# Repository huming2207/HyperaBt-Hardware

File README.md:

# HyperaBt-Hardware

Converting USB Keyboard to Bluetooth, for PC, smart phones and tablets!

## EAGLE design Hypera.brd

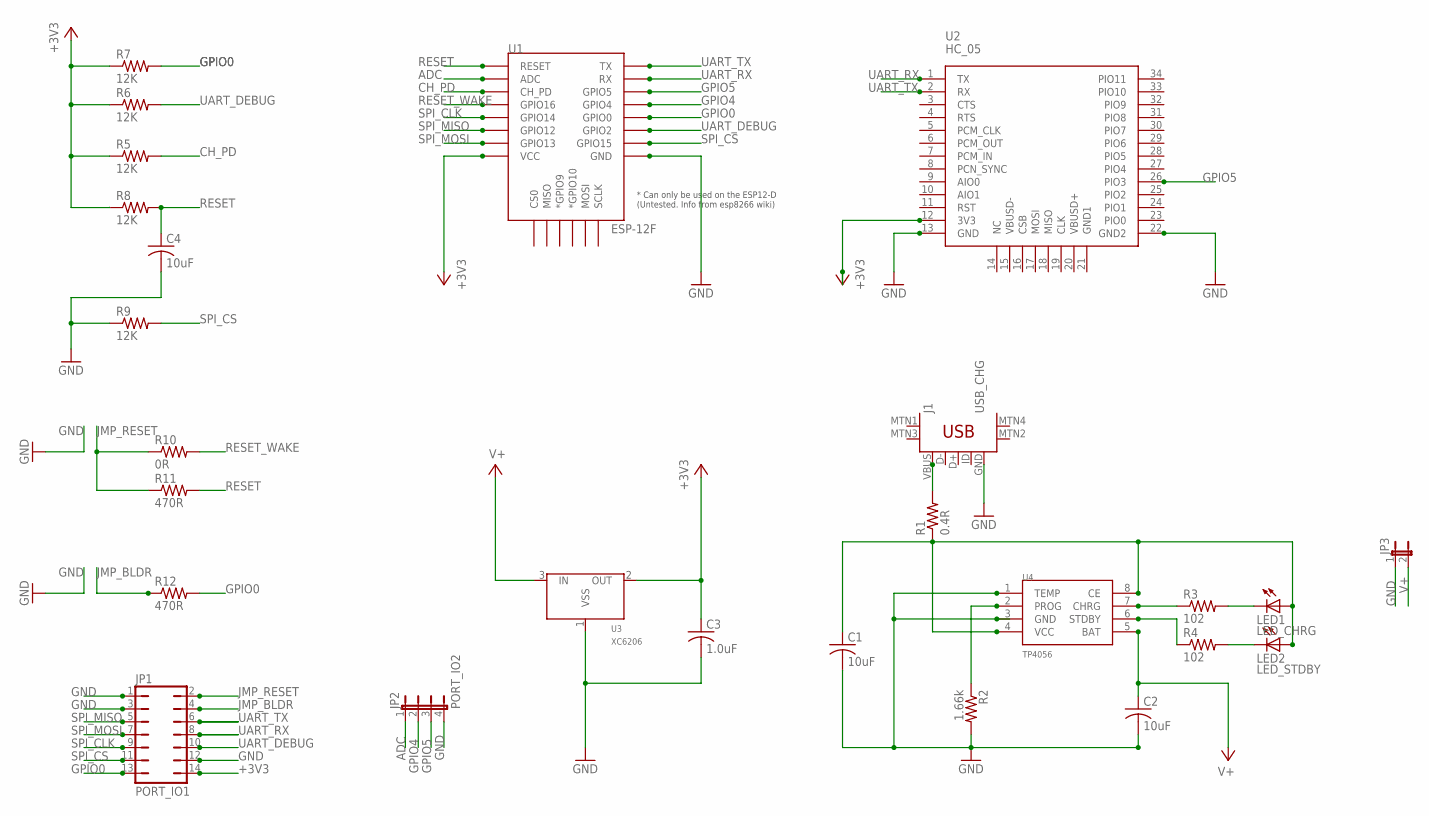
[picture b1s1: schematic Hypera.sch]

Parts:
C1, C2, C4: 10uF; C0805
C3: 1.0uF; C0805K
J1: USB_CHG; USB-MINIB
JP1: PORT_IO1; JP7Q
JP2: PORT_IO2; JP4
JP3: JP1E; JP1
LED1: LED_CHRG; CHIPLED_0805
LED2: LED_STDBY; CHIPLED_0805
R1: 0.4R; R1210
R2: 1.66k; M0805
R3, R4: 102; M0805
R5, R6, R7, R8, R9: 12K; R0805
R10: 0R; R0805
R11, R12: 470R; R0805
U1: ESP-12F; ESP12E-SMD
U2: HC_05; BLUETOOTH_SMD
U3: XC6206; XC6206_SOT-23
U4: TP4056; SOP-8

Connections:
+3V3: C3.1, JP1.14, R5.1, R6.1, R7.1, R8.1, U1.VCC, U2.12 (3V3), U3.2 (OUT)
ADC: JP2.1, U1.ADC
CH_PD: R5.2, U1.CH_PD
GND: C1.2, C2.2, C3.2, C4.2, J1.GND, JP1.1, JP1.3, JP1.12, JP2.4, JP3.1, R2.2, R9.1, U1.GND, U2.13 (GND), U2.22 (GND2), U3.1 (VSS), U4.1 (TEMP), U4.3 (GND)
GPIO0: JP1.13, R7.2, R12.2, U1.GPIO0
GPIO4: JP2.2, U1.GPIO4
GPIO5: JP2.3, U1.GPIO5, U2.26 (PIO3)
JMP_BLDR: JP1.4, R12.1
JMP_RESET: JP1.2, R10.1, R11.1
unnamed: LED2.C, R4.2
unnamed: LED1.C, R3.2
unnamed: R4.1, U4.6 (STDBY)
unnamed: R3.1, U4.7 (CHRG)
unnamed: R2.1, U4.2 (PROG)
unnamed: C1.1, LED1.A, LED2.A, R1.1, U4.4 (VCC), U4.8 (CE)
unnamed: J1.VBUS, R1.2
RESET: C4.1, R8.2, R11.2, U1.RESET
RESET_WAKE: R10.2, U1.GPIO16
SPI_CLK: JP1.9, U1.GPIO14
SPI_CS: JP1.11, R9.2, U1.GPIO15
SPI_MISO: JP1.5, U1.GPIO12
SPI_MOSI: JP1.7, U1.GPIO13
UART_DEBUG: JP1.10, R6.2, U1.GPIO2
UART_RX: JP1.8, U1.RXD0 (RX), U2.1 (TX)
UART_TX: JP1.6, U1.TXD0 (TX), U2.2 (RX)
V+: C2.1, JP3.2, U3.3 (IN), U4.5 (BAT)

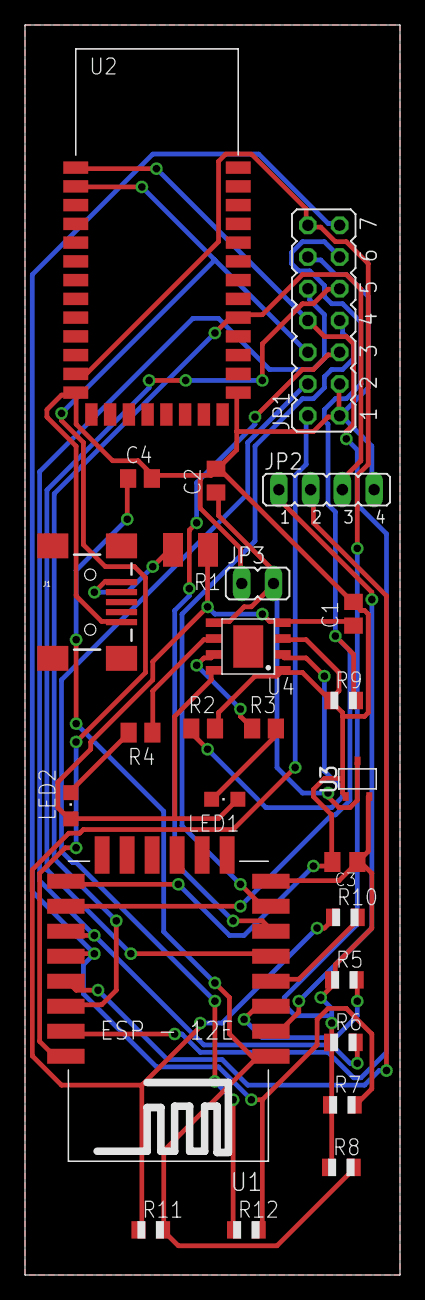
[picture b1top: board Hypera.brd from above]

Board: 2 copper layers, 30.0 x 100.0 mm, 26 parts (0 on the bottom side), 26 nets.

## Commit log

2016-11-03 Initial commit for HyperaBt hardware repo
2016-11-03 remove gerber draft zip archive

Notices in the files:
Hypera.brd:
CC-BY-NC-SA 3.0,
for educational purposes only
parts and their libraries:
SparkFun-Connectors: Licensing: Creative Commons ShareAlike 4.0 International - https://creativecommons.org/licenses/by-sa/4.0
